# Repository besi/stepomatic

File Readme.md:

# Stepomatic

Wifi-enabled 28BYJ-48 stepper motor driver.

## Pinout

| Function   | Pin    |
|:-----------|-------:|
| Motor 1    | 13     |
| Motor 2    | 12     |
| Motor 3    | 14     |
| Motor 4    | 15     |
| SDA        | 4      |
| SCL        | 5      |
| Mode       | 0      |
| Neopixel   | 16     |
| Enable IR  | 2      |
| Distance   | ADC(0) |

The IR diode can be enabled by pulling `IO2` to `0`.

The SDA and SCL need to be pulled high in software.

## Flashing

The used ESP-07 chip uses 1MB of flash so make sure to flash it with the [1MB flash image](https://micropython.org/download/ESP8266_GENERIC/).

## JLC Componennts

    # Put this in your ~/.zshrc or ~/.bashrc
    alias jlc='JLC2KiCadLib -dir lib'
    
    # Now the following will download kicad symbols, footprints and 3d models
    jlc C82227

## Acknowledgments

- Special thanks to Valentyna M. for designing the pcb artwork.
- The free font [Dexotick](https://www.behance.net/dhanstudio) was used for the pcb artwork.
- [JLC2KiCadLib](https://pypi.org/project/JLC2KiCadLib) was used for downloading the footprints for the LCSC footprints

## Known issues

The Neopixel on Pin 16 does not work since that Pin has some limitations and neither supports PWM or I2C.

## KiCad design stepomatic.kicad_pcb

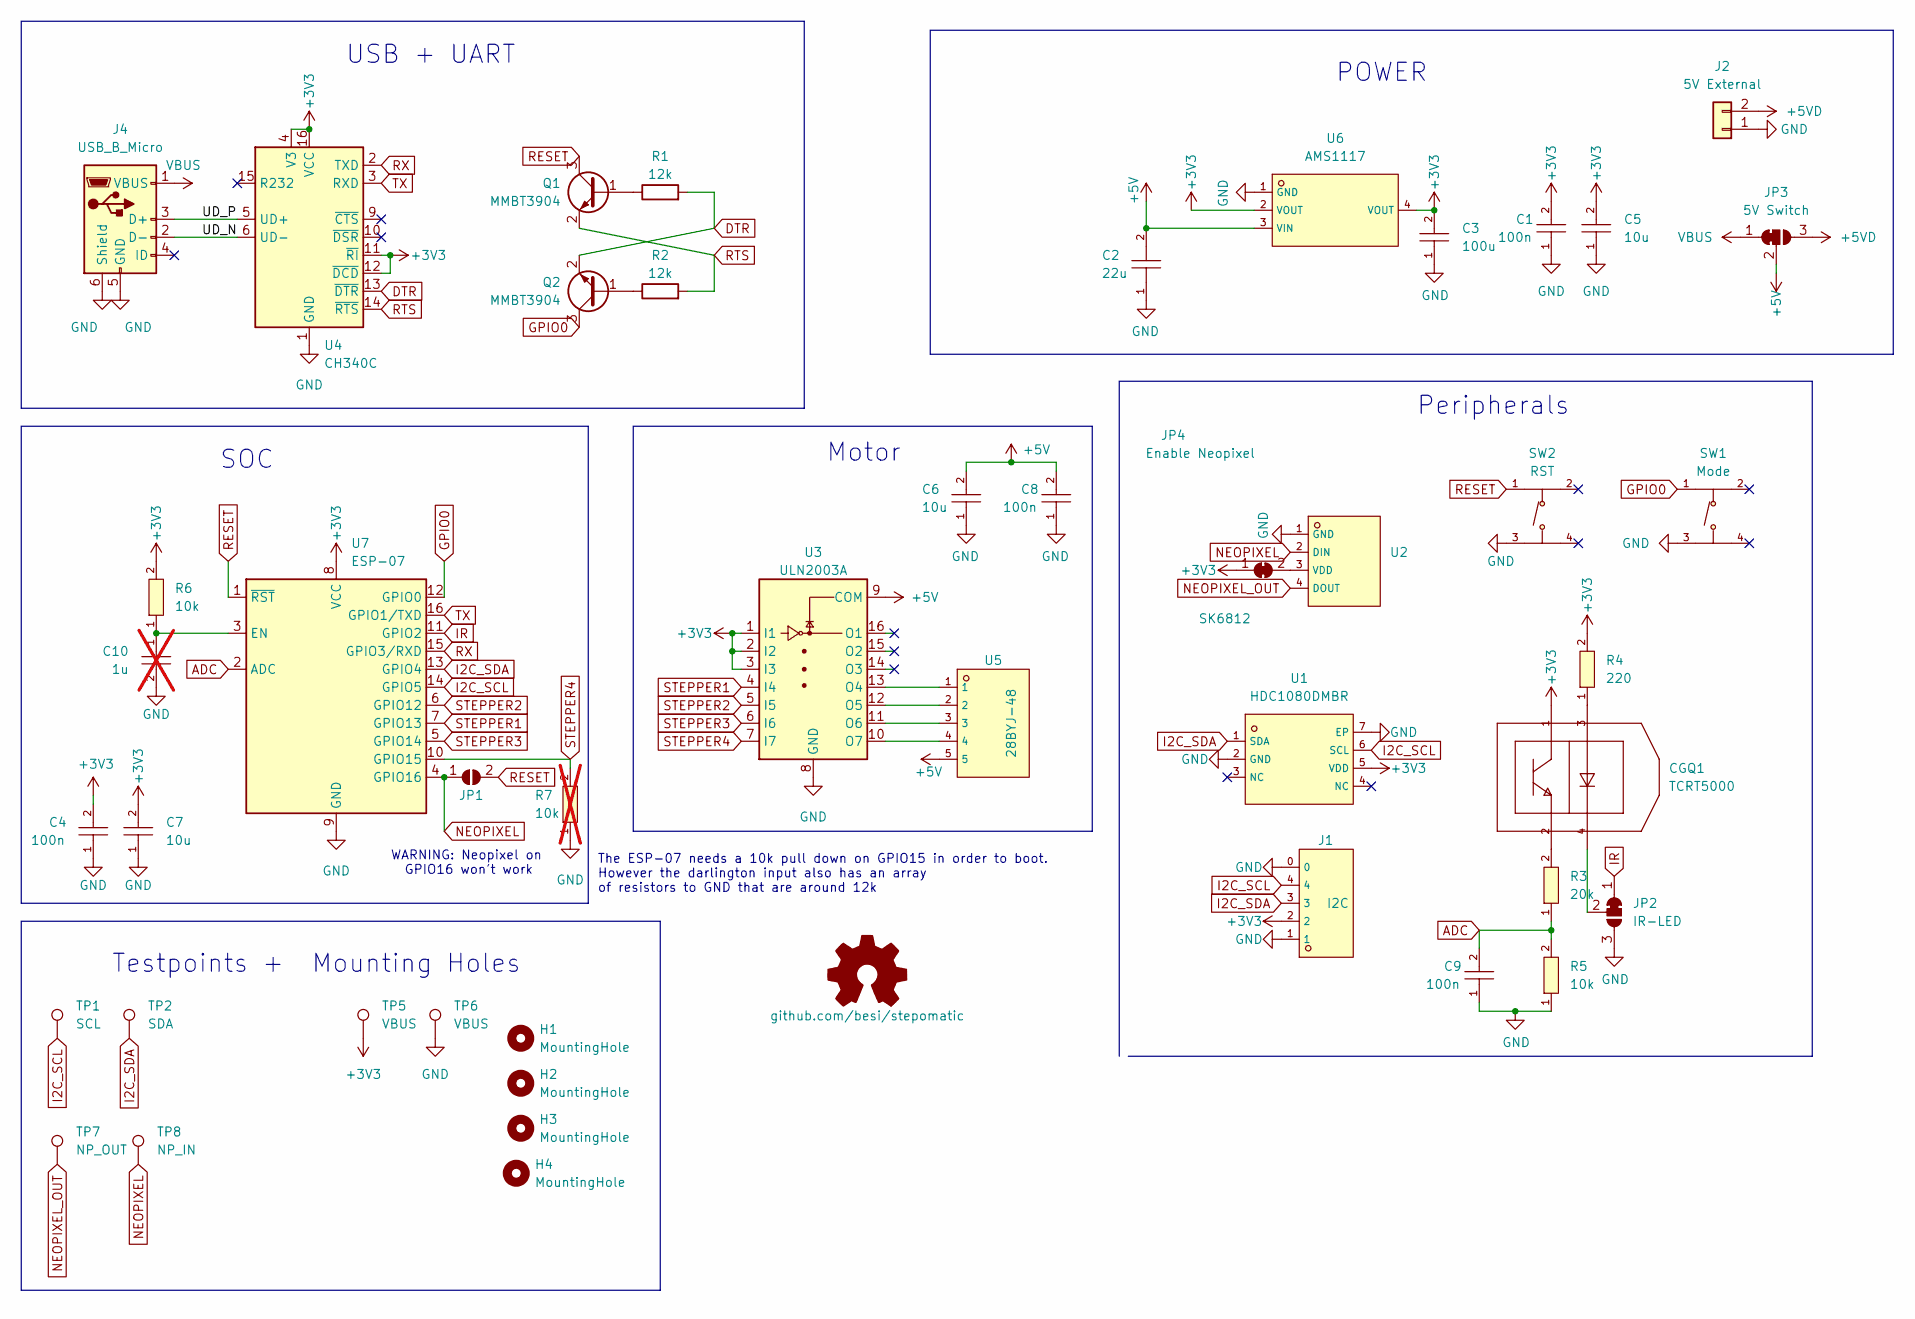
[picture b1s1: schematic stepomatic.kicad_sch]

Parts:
C1, C4, C8, C9: 100n; C0402; LCSC C1525
C2: 22u; C0603; LCSC C59461
C3: 100u; C1206; LCSC C15008
C5, C6, C7: 10u; C0402; LCSC C15525
C10: 1u; C0603; LCSC C15849; not fitted
CGQ1: TCRT5000; OPTO-TH_TCRT5000L; LCSC C24085
H1, H2, H3, H4: MountingHole; MountingHole_3.2mm_M3; LCSC DNP
J1: I2C; CONN-SMD_BM04B-SRSS-TB; LCSC C160390
J2: 5V External; PinHeader_1x02_P2.54mm_Horizontal
J4: USB_B_Micro; USB_Micro-B_Molex-105017-0001; LCSC C505111
JP1: Deep Sleep; SolderJumper-2_P1.3mm_Open_TrianglePad1.0x1.5mm; LCSC DNP
JP2: IR-LED; SolderJumper-3_P1.3mm_Bridged12_RoundedPad1.0x1.5mm
JP3: 5V Switch; SolderJumper-3_P1.3mm_Bridged12_RoundedPad1.0x1.5mm
JP4: Enable Neopixel; SolderJumper-2_P1.3mm_Bridged_RoundedPad1.0x1.5mm
OSHW1: github.com/besi/stepomatic; OSHW-Symbol_6.7x6mm_SilkScreen
Q1, Q2: MMBT3904; SOT-23-3_L2.9-W1.3-P1.90-LS2.4-BR; LCSC C20526
R1, R2: 12k; C0402; LCSC C25752
R3: 20k; R0603; LCSC C4184
R4: 220; R0603; LCSC C22962
R5, R6: 10k; R0603; LCSC C25804
R7: 10k; R0603; LCSC C25804; not fitted
SW1: Mode; SW-SMD_4P-L5.1-W5.1-P3.70-LS6.5-TL-2; LCSC C318884
SW2: RST; SW-SMD_4P-L5.1-W5.1-P3.70-LS6.5-TL-2; LCSC C318884
TP1: SCL; TestPoint_Pad_D1.0mm
TP2: SDA; TestPoint_Pad_D1.0mm
TP5, TP6: VBUS; TestPoint_Pad_D1.0mm
TP7: NP_OUT; TestPoint_Pad_D1.0mm
TP8: NP_IN; TestPoint_Pad_D1.0mm
U1: HDC1080DMBR; SENSOR-SMD_HDC1080DMBR; LCSC C82227
U2: SK6812; LED-SMD_4P-L3.5-W3.5-BR_SK6812MINI-HS; LCSC C2922787
U3: ULN2003A; SOIC-16_3.9x9.9mm_P1.27mm; LCSC C7512
U4: CH340C; SOIC-16_3.9x9.9mm_P1.27mm; LCSC C7464026
U5: 28BYJ-48; CONN-TH_B5B-XH-A-LF-SN; LCSC C157991
U6: AMS1117; SOT-223-3_L6.5-W3.4-P2.30-LS7.0-BR; LCSC C6186
U7: ESP-07; WIFIM-SMD_ESP-07; LCSC C82894

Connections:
+3V3: C1.2, C3.2, C4.2, C5.2, C7.2, CGQ1.1 (C), J1.2, JP4.1 (A), R4.2, R6.2, TP5.1, U1.5 (VDD), U3.1 (I1), U3.2 (I2), U3.3 (I3), U4.4 (V3), U4.11 (~RI), U4.12 (~DCD), U4.16 (VCC), U6.2 (VOUT), U6.4 (VOUT), U7.8 (VCC)
+5V: C2.2, C6.2, C8.2, JP3.2 (C), U3.9 (COM), U5.5, U6.3 (VIN)
+5VD: J2.2, JP3.3 (B)
/UD_N: J4.2 (D-), U4.6 (UD-)
/UD_P: J4.3 (D+), U4.5 (UD+)
ADC: C9.2, R3.1, R5.2, U7.2 (ADC)
DTR: Q2.2 (E), R1.2, U4.13 (~DTR)
GND: C1.1, C2.1, C3.1, C4.1, C5.1, C6.1, C7.1, C8.1, C9.1, C10.2, J1.0, J1.1, J2.1, J4.5 (GND), J4.6 (Shield), JP2.3 (B), R5.1, R7.1, SW1.3 (C), SW2.3 (C), TP6.1, U1.2 (GND), U1.7 (EP), U2.1 (GND), U3.8 (GND), U4.1 (GND), U6.1 (GND), U7.9 (GND)
GPIO0: Q2.3 (C), SW1.1 (A), U7.12 (GPIO0)
I2C_SCL: J1.4, TP1.1, U1.6 (SCL), U7.14 (GPIO5)
I2C_SDA: J1.3, TP2.1, U1.1 (SDA), U7.13 (GPIO4)
IR: JP2.1 (A), U7.11 (GPIO2)
NEOPIXEL: JP1.1 (A), TP8.1, U2.2 (DIN), U7.4 (GPIO16)
NEOPIXEL_OUT: TP7.1, U2.4 (DOUT)
unnamed: CGQ1.3 (A), R4.1
unnamed: CGQ1.2 (E), R3.2
unnamed: CGQ1.4 (C), JP2.2 (C)
unnamed: JP4.2 (B), U2.3 (VDD)
unnamed: Q1.1 (B), R1.1
unnamed: Q2.1 (B), R2.1
unnamed: U3.13 (O4), U5.1
unnamed: U3.12 (O5), U5.2
unnamed: U3.11 (O6), U5.3
unnamed: U3.10 (O7), U5.4
unnamed: C10.1, R6.1, U7.3 (EN)
RESET: JP1.2 (B), Q1.3 (C), SW2.1 (A), U7.1 (~RST)
RTS: Q1.2 (E), R2.2, U4.14 (~RTS)
RX: U4.2 (TXD), U7.15 (GPIO3/RXD)
STEPPER1: U3.4 (I4), U7.7 (GPIO13)
STEPPER2: U3.5 (I5), U7.6 (GPIO12)
STEPPER3: U3.6 (I6), U7.5 (GPIO14)
STEPPER4: R7.2, U3.7 (I7), U7.10 (GPIO15)
TX: U4.3 (RXD), U7.16 (GPIO1/TXD)
VBUS: J4.1 (VBUS), JP3.1 (A)

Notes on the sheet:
WARNING: Neopixel on GPIO16 won't work
POWER
USB + UART
Peripherals
The ESP-07 needs a 10k pull down on GPIO15 in order to boot. However the darlington input also has an array of resistors to GND that are around 12k
Motor
SOC
Testpoints + Mounting Holes

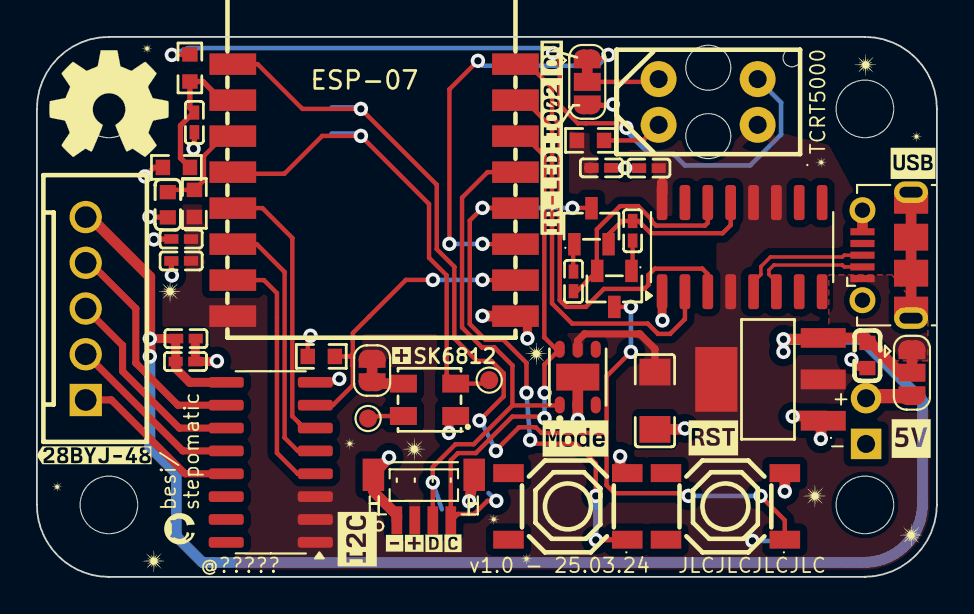
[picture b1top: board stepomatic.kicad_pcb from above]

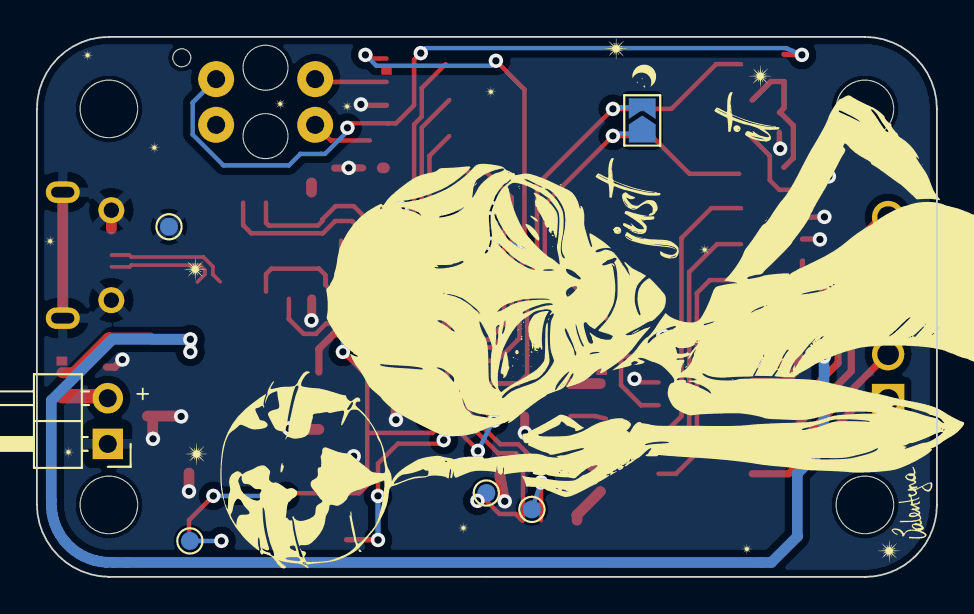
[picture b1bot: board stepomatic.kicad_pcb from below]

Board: 2 copper layers, 50.0 x 30.0 mm, 59 parts (6 on the bottom side), 34 nets.

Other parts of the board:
kibuzzard-65D87D0C: G***; kibuzzard-65D87D0C
kibuzzard-65D87D4C: G***; kibuzzard-65D87D4C
kibuzzard-65D87D42: G***; kibuzzard-65D87D42
kibuzzard-65D87D58: G***; kibuzzard-65D87D58
kibuzzard-65D87D77: G***; kibuzzard-65D87D77
kibuzzard-65DB2C8E: G***; kibuzzard-65DB2C8E
kibuzzard-65DB2C89: G***; kibuzzard-65DB2C89
kibuzzard-65DB2C93, kibuzzard-65DB2C93#2: G***; kibuzzard-65DB2C93
kibuzzard-65DB2CAC: G***; kibuzzard-65DB2CAC
kibuzzard-65EA2F1C: G***; kibuzzard-65EA2F1C
kibuzzard-65F0E053: G***; kibuzzard-65F0E053

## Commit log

2024-02-10 Add components and do routing
2024-02-12 Re-layout
2024-02-12 Prepare for jlc submission
2024-02-12 Add voltage divider for ADC
2024-02-12 Add neopixel
2024-02-12 Add I2C footprint
2024-02-12 Fix wrong capacitor
2024-02-12 Remove JLC property
2024-02-12 Fix rotation of I2C connector
2024-02-12 Secure 3V3 connections and change the way the ADC is read
2024-02-12 Add 200k because of saturation voltage of the photo transistor
2024-02-12 Include neopixel and fix package of C3 100uF
2024-02-12 Fix package of C3
2024-02-12 Allow to switch between ON and GPIO02 for IR send
2024-02-12 Tidy up
2024-02-12 Fix orientation of the stepper motor plug
2024-02-13 Tidy up for review
2024-02-13 Tidy
2024-02-13 Add JLC part for neopixel
2024-02-13 Add EP pad of HDC1080DMBR
2024-02-13 Use differential pair wiring for USB
2024-02-13 Remove todos
2024-02-13 Only use JLC footprints
2024-02-19 Add pcb artwork and some 5V caps
2024-02-25 Add oshw logo, silkscreen improvements capacitor for adc
2024-02-25 Prettify schematic
2024-02-26 Silkscreen
2024-02-26 Minor changes on PCB
2024-02-27 Exclude unpopulatable components from BOM
2024-02-27 Finish up PCB backside artwork
2024-02-28 Add artists signature
2024-02-28 Add acknoledements
2024-02-28 Add commit label
2024-02-28 Clean up silkscreen
2024-02-28 Release candidate v1.0
2024-03-01 Change resistors on TCRT5000 to 20k and 10k
2024-03-01 Add neopixel testpads
2024-03-01 SK6812-HS
2024-03-01 Make IO2 the default for the TCRT5000
2024-03-01 Update version
2024-03-07 Last twaks
    Add a jumper to disable the Neopixel
2024-03-07 JLC Order 7.03.2024
2024-03-07 Exclude jumper from bom
2024-03-07 Fix name of Jumper
2024-03-07 Add OSHW Logo
2024-03-07 More comprehensive 5V switch
2024-03-10 Pre production
2024-03-10 Production files
2024-03-11 Exclude OSHW logo
2024-03-14 Add backside image
2024-03-21 Add pulldown for GPIO15
2024-03-21 Add commit sha
2024-03-21 Add a 10k pull down on GPIO15 but don’t populate it since the darlington array has a series resistance to GND of ~12k itself.
2024-03-25 Add a RC circuit to the EN pin
2024-03-25 Remove the git comment from the version section
2024-04-12 Add 3d rendering of the pcb
2024-04-12 More generic .gitignore
2024-04-12 Add software libraries
2024-05-07 Add drill origin in the center of the board
2024-05-07 Update Readme.md
    Fix a typo
2024-05-07 Update main.py to add more demo code
2024-05-07 Add Step file
2025-01-08 Add IR and temperature examples
2025-01-08 Added warning about neopixel
2025-03-01 Kicad 8
2025-03-05 Update main command
    # Conflicts:
    # sw/main.py
2025-03-05 Rework 1, per EE SO answer.
    Ground plane has integrity now.
    +3.3V plane flows better.
    Note: CH340C pins 11 and 12 are inputs, thus 3.3V can be routed through them. Similarly, ULN2003 pins 1-3 are inputs, and 3.3V can pass through them.
    Finally, thermal breaks are not really needed for SMT parts.
2025-03-15 Add note about flash size
2025-03-27 Make the stepper run faster
2025-03-27 Add known issues section to the Readme
2025-03-27 Add pinout to the readme
